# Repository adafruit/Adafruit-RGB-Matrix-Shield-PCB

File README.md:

## Adafruit RGB Matrix Display Shield PCB

<a href="http://www.adafruit.com/products/2601"><br/>
Click here to purchase one from the Adafruit shop</a>

PCB files for the Adafruit RGB Matrix Shield. PCB format is EagleCAD schematic and board layout

For more details, check out the product page at
* https://www.adafruit.com/product/2601

### Description

Our RGB matricies are dazzling, with their hundreds or even thousands of individual RGB LEDs. Compared to NeoPixels, they've got great density, power usage and the price-per-LED can't be beat. But...(isn't there always a but?) You need to use our special library to control them and they require a bunch of wires to be plugged in. Tougher than a single-wire connection for sure.

If you've got an Arduino-compatible board, with an ATmega328p chip (like our Metro 328) or SAMD21 (like the Metro M0) or even SAMD51 (like our Metro M4) this shield will make usage a snap! A little light soldering to attach the headers, connector and terminal block and you're ready to rock. Plug it onto your microcontroller board, and you'll be able to attach any RGB matrix with ease. This shield just takes care of the wiring for you!

For 800mA or less power usage on the matrix you can even 'borrow' the 5V power from the Arduino's regulator. This isn't good for projects where you have a lot of LEDs on at once but for scrolling text and light LED usage it will make wiring even easier because you dont need a separate power adapter. Of course, if you need 1 Amp or more, just use the 2x8 connector for data and use a separate 5V 2A or 5V 4A wall adapter directly to the panel.

Note that this shield is just a wiring adapter, if you have a Metro 328 you can only use 16x32 or possibly 32x32 matrices before you run out of RAM. For big panels, use a Metro M0 or M4 - those will work best thanks to their enormous RAM.

**Please note our Arduino library only supports 32-pixel tall matrices, so don't try using a 64x64 matrix, it doesn't work!**

### License

Adafruit invests time and resources providing this open source design, please support Adafruit and open-source hardware by purchasing products from [Adafruit](https://www.adafruit.com)!

Designed by Limor Fried/Ladyada for Adafruit Industries.

Creative Commons Attribution/Share-Alike, all text above must be included in any redistribution. See license.txt for additional details.

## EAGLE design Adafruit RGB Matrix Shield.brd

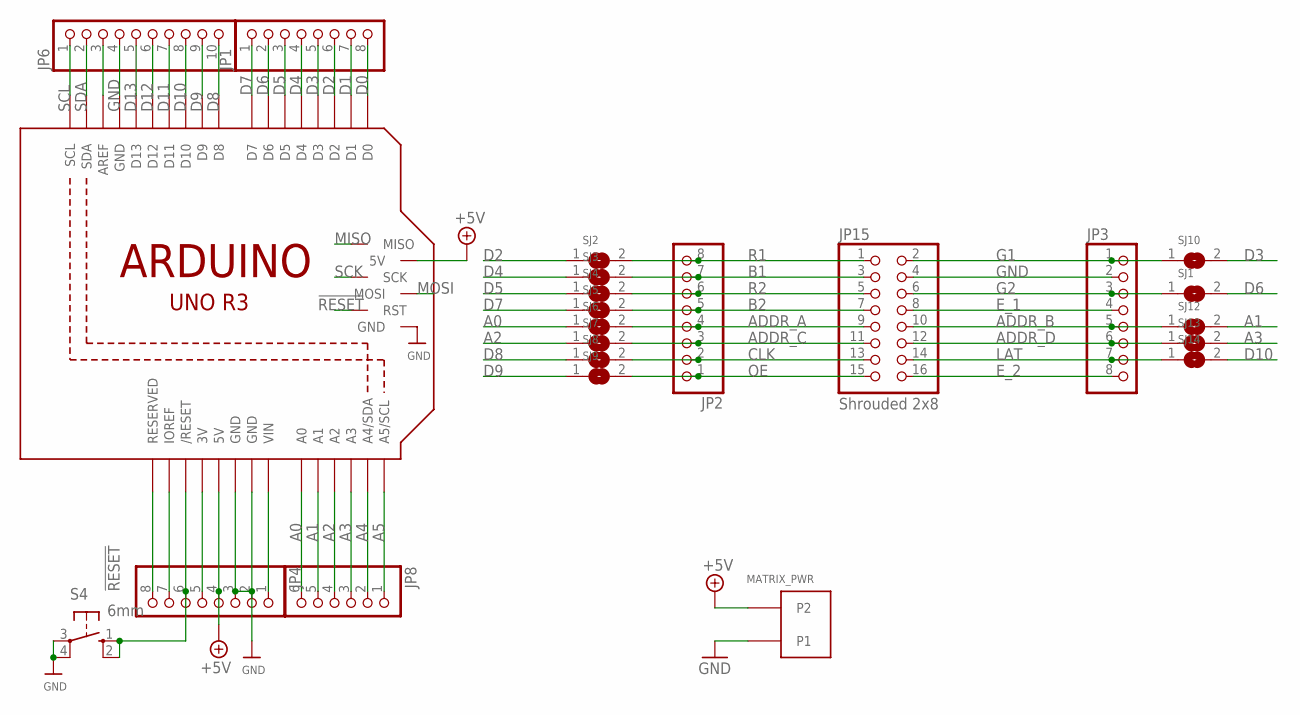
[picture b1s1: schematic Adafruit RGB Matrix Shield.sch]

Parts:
JP1, JP4: PINHD-1X8CLEANBIG; 1X08-CLEANBIG
JP2, JP3: HEADER-1X876MIL; 1X08_ROUND_76
JP6: HEADER-1X1070MIL; 1X10_ROUND70
JP8: PINHD-1X6CB; 1X06-CLEANBIG
JP15: Shrouded 2x8; 2X08_SHROUDED
MATRIX_PWR: PINHEAD; TERMBLOCK508
S4: 6mm; B3F-10XX
SJ1, SJ2, SJ3, SJ4, SJ5, SJ6, SJ7, SJ8, SJ9, SJ10, SJ12, SJ13, SJ14: SOLDERJUMPERCLOSED; SOLDERJUMPER_CLOSEDWIRE
U$41: ARDUINO_R3_ICSP_NODIM; ARDUINOR3_ICSP_NODIM

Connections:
!RESET: JP4.6, S4.1 (S), S4.2 (S1), U$41.RESET (/RESET), U$41.RESET_ICSP (RST)
+3V: JP4.5, U$41.3V
+5V: JP4.4, MATRIX_PWR.P$4 (P2), U$41.5V, U$41.5V_ICSP (5V)
A0: JP8.6, SJ6.1, U$41.A0
A1: JP8.5, SJ12.2, U$41.A1
A2: JP8.4, SJ7.1, U$41.A2
A3: JP8.3, SJ13.2, U$41.A3
A4: JP8.2, U$41.A4 (A4/SDA)
A5: JP8.1, U$41.A5 (A5/SCL)
ADDR_A: JP2.4, JP15.9, SJ6.2
ADDR_B: JP3.5, JP15.10, SJ12.1
ADDR_C: JP2.3, JP15.11, SJ7.2
ADDR_D: JP3.6, JP15.12, SJ13.1
AREF: JP6.3, U$41.AREF
B1: JP2.7, JP15.3, SJ3.2
B2: JP2.5, JP15.7, SJ5.2
CLK: JP2.2, JP15.13, SJ8.2
D0: JP1.8, U$41.D0
D1: JP1.7, U$41.D1
D2: JP1.6, SJ2.1, U$41.D2
D3: JP1.5, SJ10.2, U$41.D3
D4: JP1.4, SJ3.1, U$41.D4
D5: JP1.3, SJ4.1, U$41.D5
D6: JP1.2, SJ1.2, U$41.D6
D7: JP1.1, SJ5.1, U$41.D7
D8: JP6.10, SJ8.1, U$41.D8
D9: JP6.9, SJ9.1, U$41.D9
D10: JP6.8, SJ14.2, U$41.D10
D11: JP6.7, U$41.D11
D12: JP6.6, U$41.D12
D13: JP6.5, U$41.D13
E_1: JP3.4, JP15.8
E_2: JP3.8, JP15.16
G1: JP3.1, JP15.2, SJ10.1
G2: JP3.3, JP15.6, SJ1.1
GND: JP3.2, JP4.2, JP4.3, JP6.4, JP15.4, MATRIX_PWR.P$3 (P1), S4.3, S4.4 (P1), U$41.GND, U$41.GND@1 (GND), U$41.GND@2 (GND), U$41.GND@3 (GND)
IOREF: JP4.7, U$41.IOREF
LAT: JP3.7, JP15.14, SJ14.1
MISO: U$41.MISO
MOSI: U$41.MOSI
NC: JP4.8, U$41.RESERVED
OE: JP2.1, JP15.15, SJ9.2
R1: JP2.8, JP15.1, SJ2.2
R2: JP2.6, JP15.5, SJ4.2
SCK: U$41.SCK
SCL: JP6.1, U$41.SCL
SDA: JP6.2, U$41.SDA
VIN: JP4.1, U$41.VIN

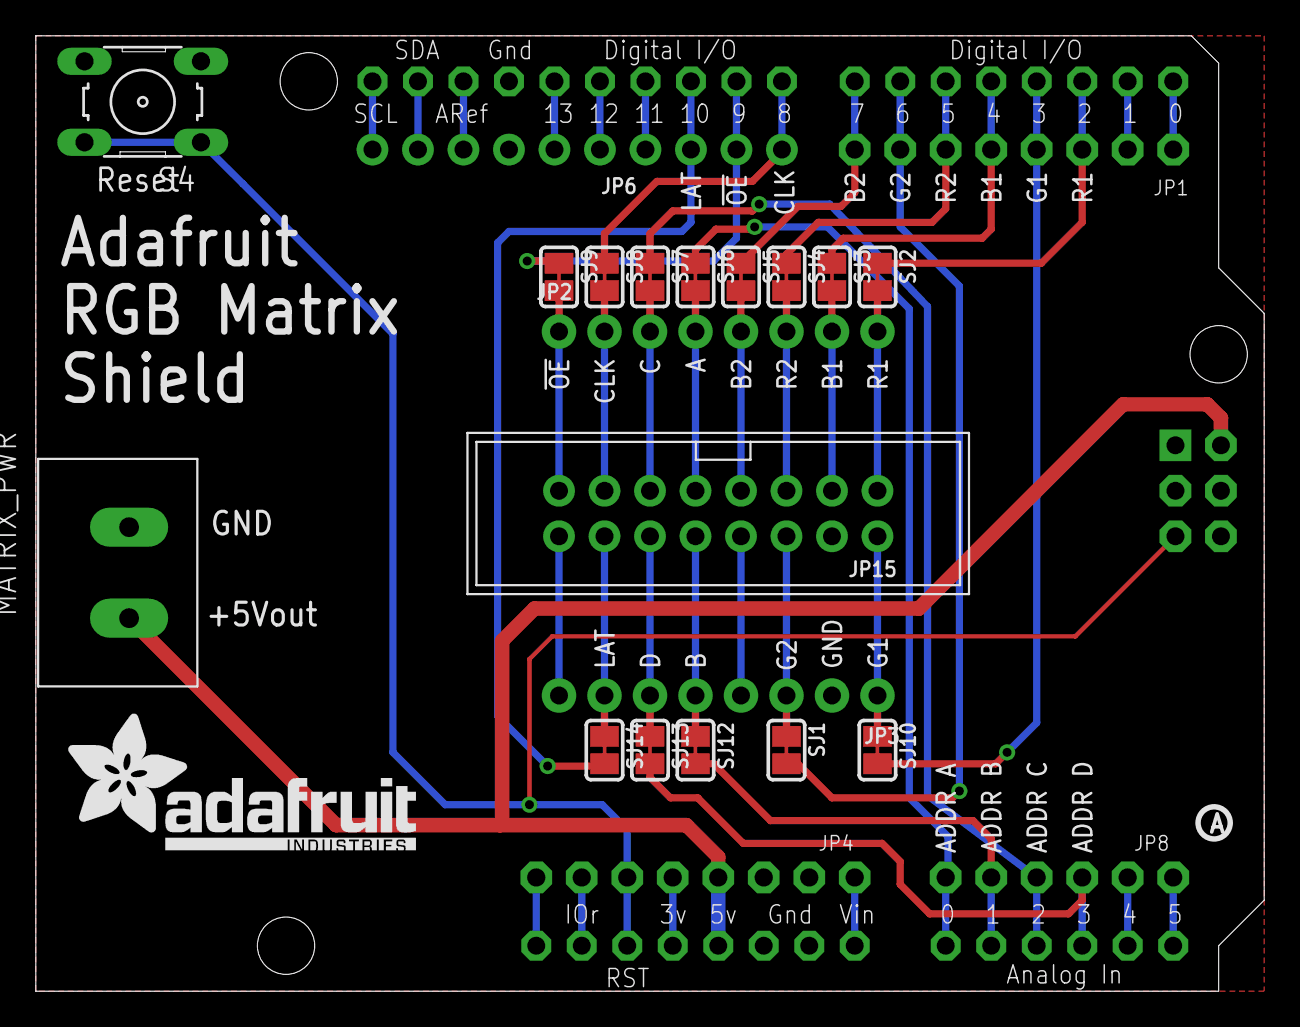
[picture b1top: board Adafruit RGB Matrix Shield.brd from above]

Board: 2 copper layers, 68.6 x 53.3 mm, 25 parts (0 on the bottom side), 45 nets.

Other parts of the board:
U$8: PCBFEAT-REV-040
U$9: ADAFRUIT_TEXT_20MM

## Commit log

2018-07-07 filez
